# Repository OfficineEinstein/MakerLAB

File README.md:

# MakerLAB
Demo board didattica per i laboratori di Tecnologie e Progettazione di Sistemi Elettronici (TPSE):  elettronica digitale e microcontrollori

Il laboratorio portatile finalmente operativo

Video testing of the MakerLAB

https://youtu.be/5uMLk8OzwR4

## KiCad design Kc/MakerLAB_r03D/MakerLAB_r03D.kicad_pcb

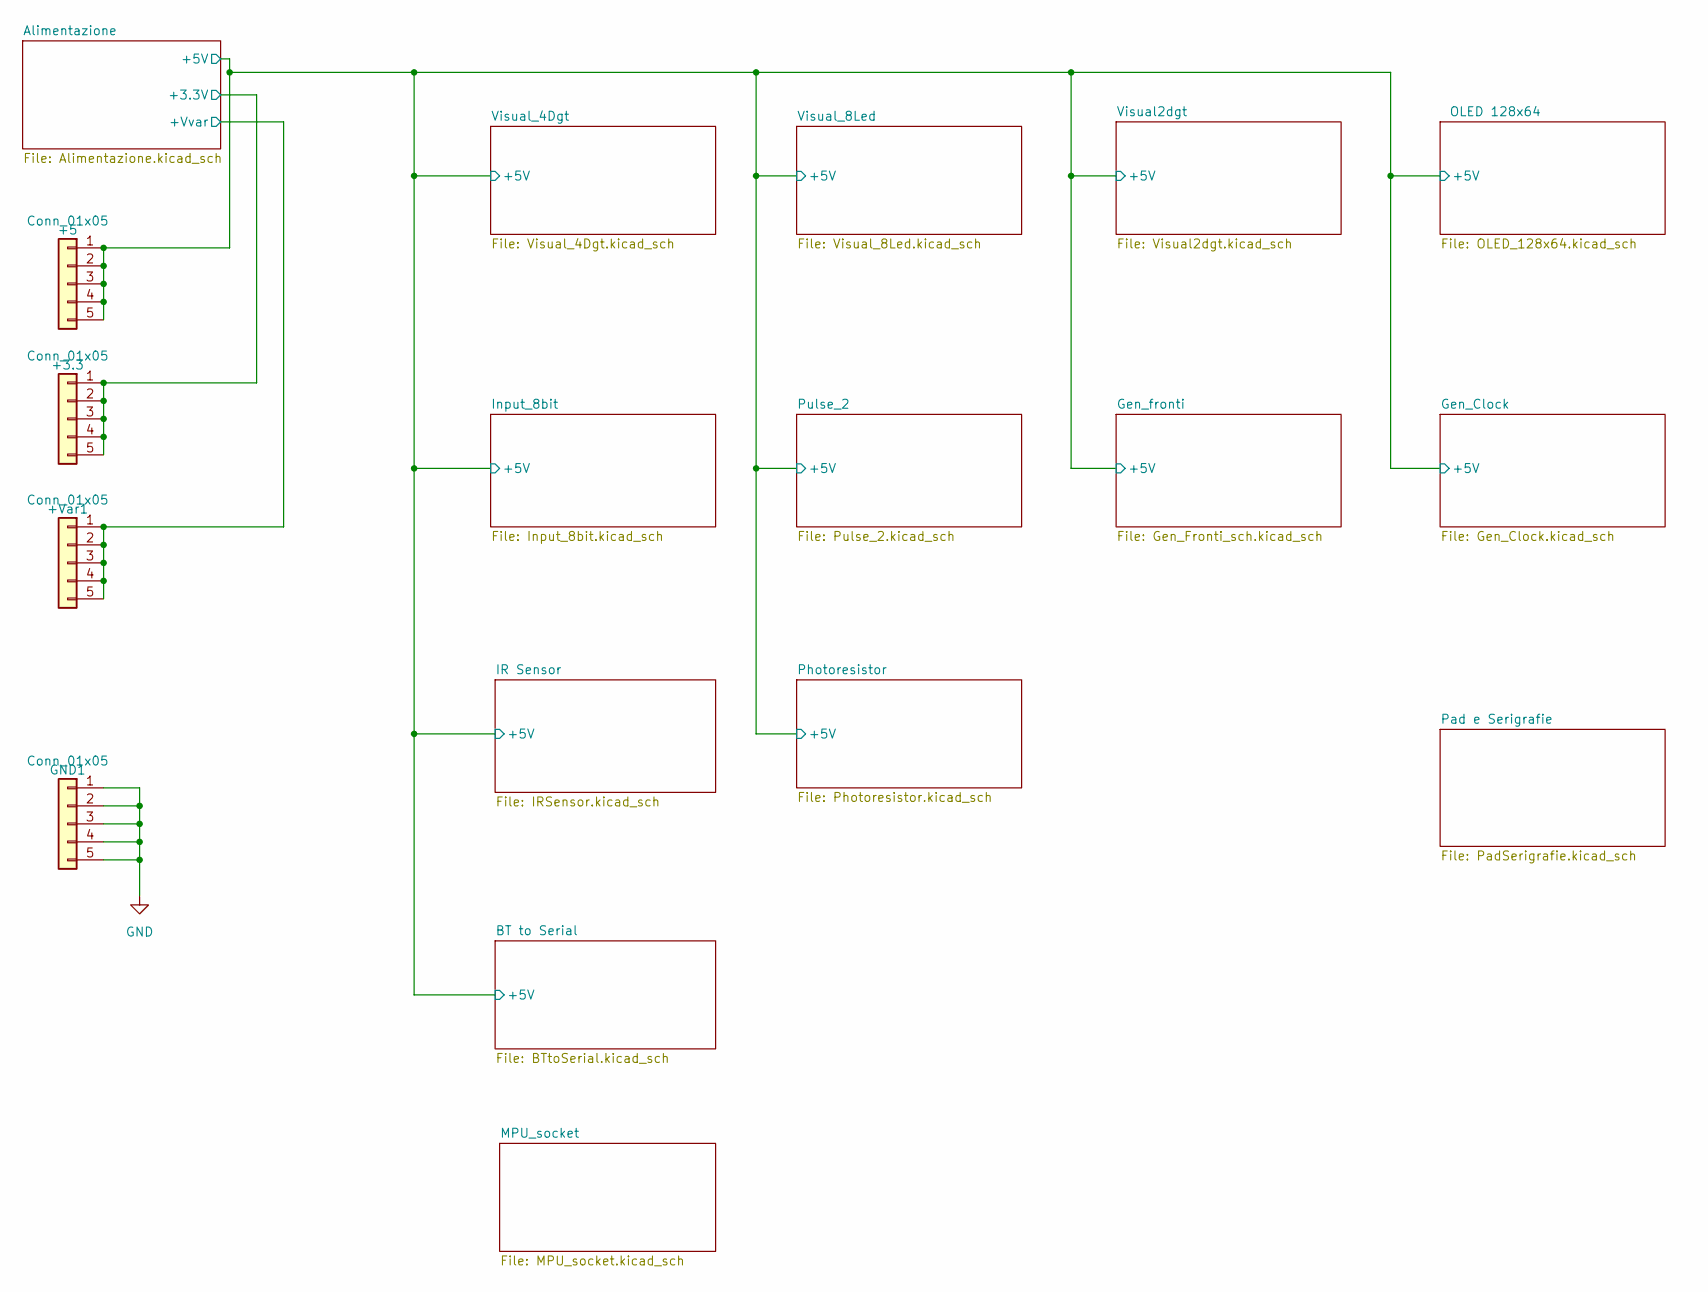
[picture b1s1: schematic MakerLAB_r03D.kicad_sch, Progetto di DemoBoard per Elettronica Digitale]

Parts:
+3.3, +5: Conn_01x05; PinHeader_1x05_P2.54mm_Vertical
+Var1: Conn_01x05; PinHeader_1x05_P2.54mm_Vertical
GND1: Conn_01x05; PinHeader_1x05_P2.54mm_Vertical

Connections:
/Alimentazione/+3.3V: +3.3.1, +3.3.2, +3.3.3, +3.3.4, +3.3.5; also elsewhere on the board
/Alimentazione/+5V: +5.1, +5.2, +5.3, +5.4, +5.5; also elsewhere on the board
/Alimentazione/+Vvar: +Var1.1, +Var1.2, +Var1.3, +Var1.4, +Var1.5; also elsewhere on the board

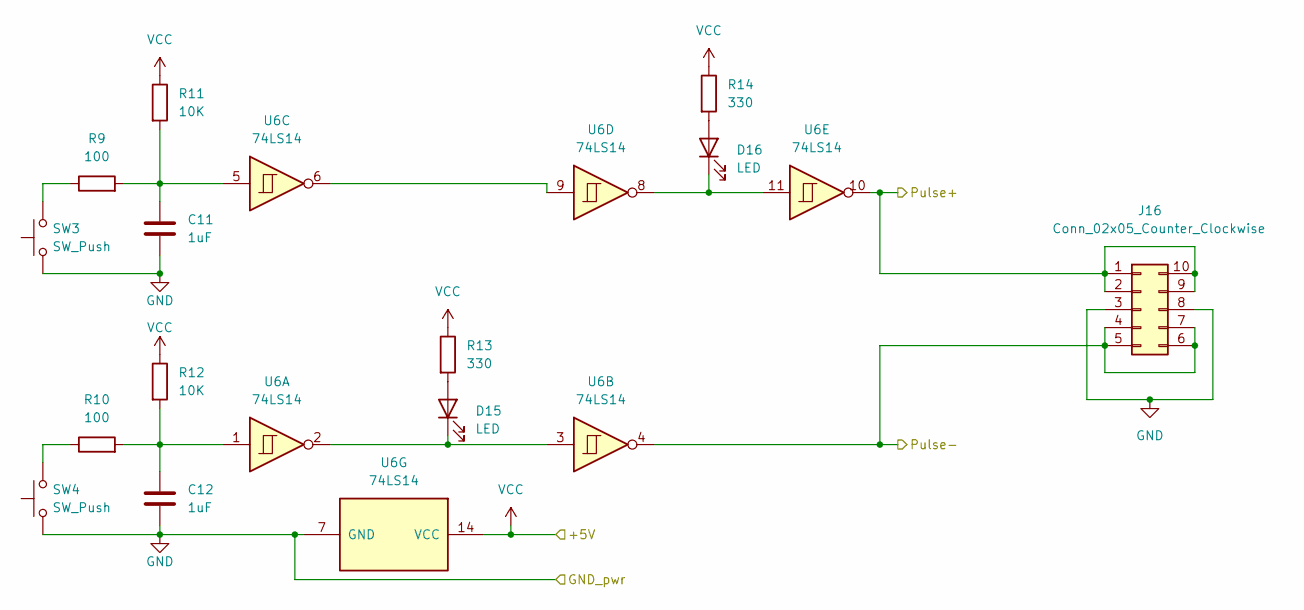
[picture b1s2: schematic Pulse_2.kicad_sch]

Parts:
C11, C12: 1uF
D15, D16: LED
J16: Conn_02x05_Counter_Clockwise; PinSocket_2x05_P2.54mm_Vertical
R9, R10: 100
R11, R12: 10K
R13, R14: 330
SW3, SW4: SW_Push
U6: 74LS14

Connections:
/Alimentazione/+5V: R11.1, R12.1, R13.1, R14.1, U6.14 (VCC); also elsewhere on the board
unnamed: C11.1, R9.2, R11.2, U6.5
unnamed: C12.1, R10.2, R12.2, U6.1
unnamed: D15.1 (K), U6.2, U6.3
unnamed: D15.2 (A), R13.2
unnamed: D16.1 (K), U6.8, U6.11
unnamed: D16.2 (A), R14.2
unnamed: R9.1, SW3.2
unnamed: R10.1, SW4.2
unnamed: U6.6, U6.9

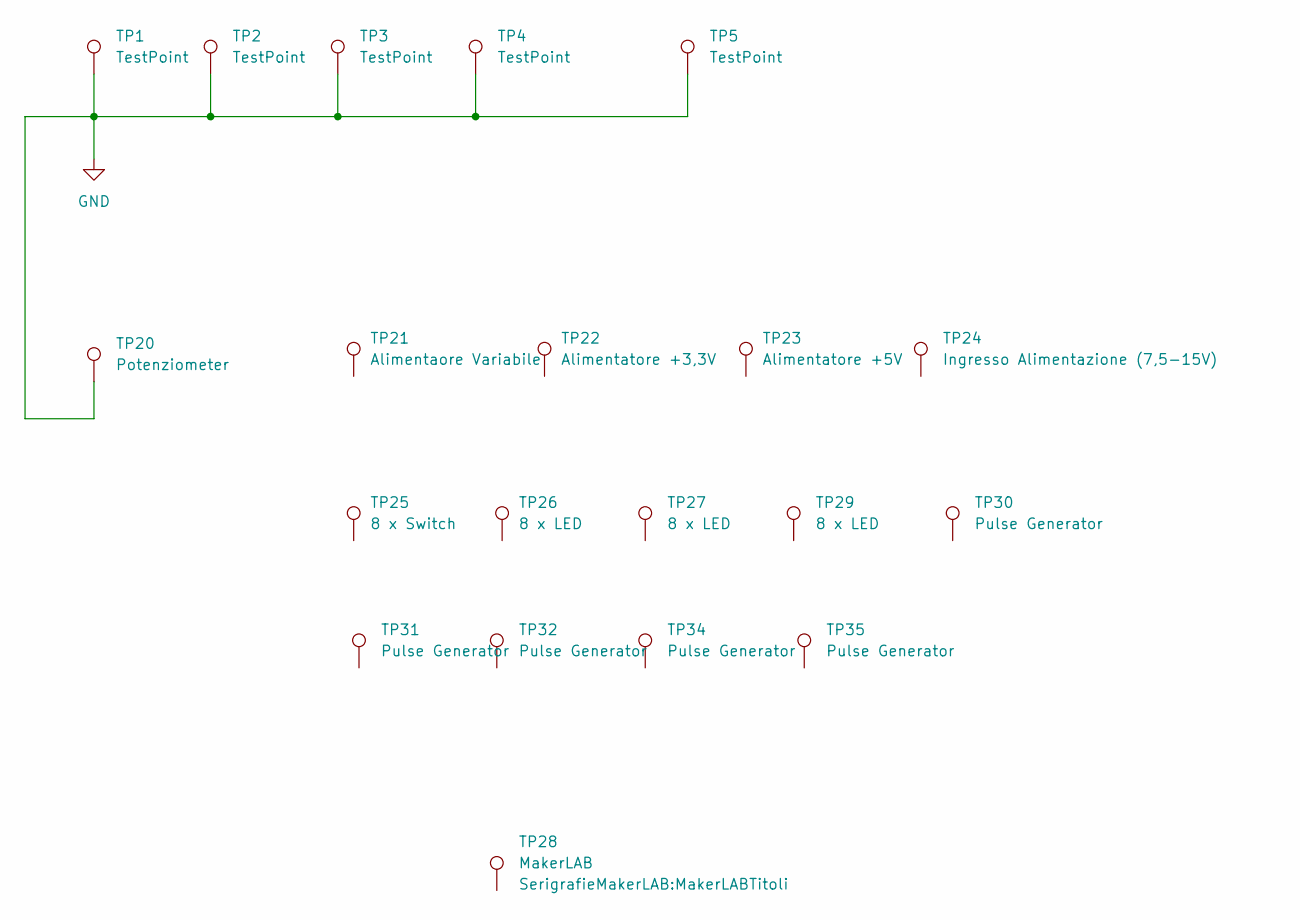
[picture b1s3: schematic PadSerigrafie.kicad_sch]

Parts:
TP1, TP2, TP3, TP4: TestPoint; MountingHole_3.2mm_M3_Pad_Via
TP5: TestPoint; BreadBoard 81x146
TP20: Potenziometer; MountingHole_6.5mm_Pad_Via
TP21: Alimentaore Variabile; Alimentatore Variabile
TP22: Alimentatore +3,3V; Alimentatore Variabile
TP23: Alimentatore +5V; Alimentatore Variabile
TP24: Ingresso Alimentazione (7,5-15V); Alimentatore Variabile
TP25: 8 x Switch; Alimentatore Variabile
TP26: 8 x LED; Alimentatore Variabile
TP27: 8 x LED; Disp4x7Seg
TP28: MakerLAB; MakerLABTitoli
TP29: 8 x LED; Clock NE555
TP30: Pulse Generator; Clock NE555
TP31, TP32, TP34, TP35: Pulse Generator; Disp4x7Seg

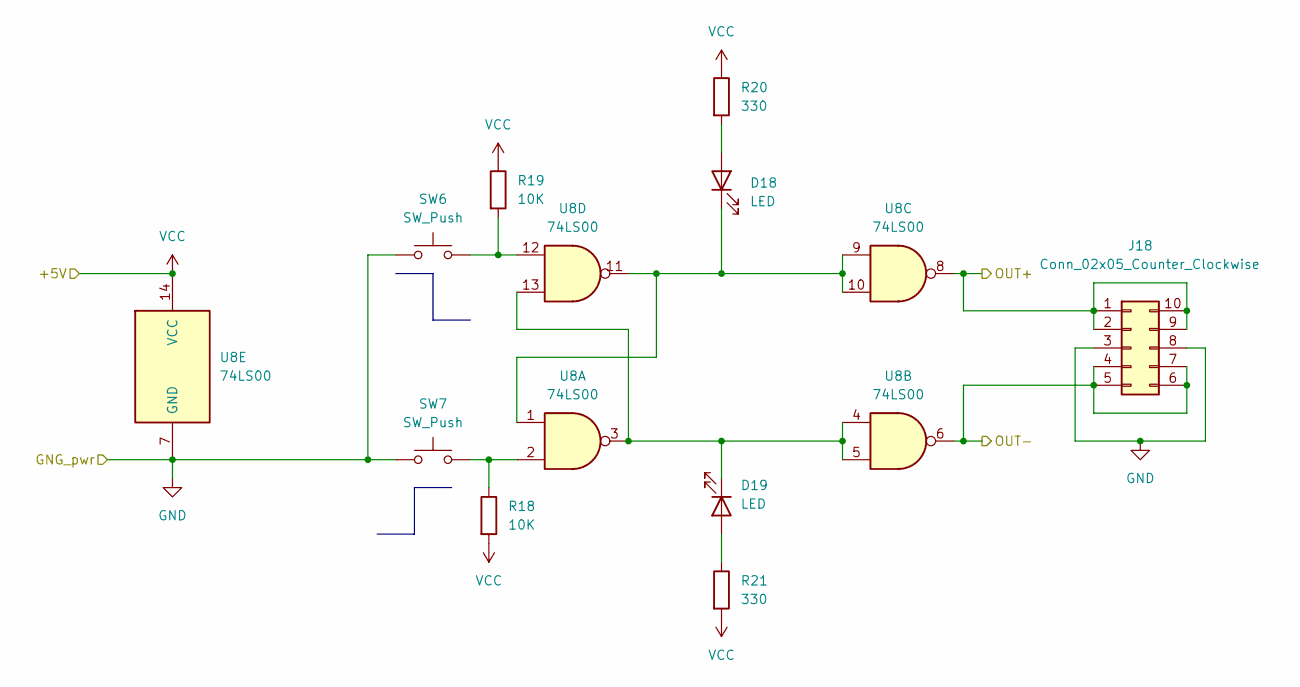
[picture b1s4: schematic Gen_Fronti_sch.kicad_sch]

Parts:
D18, D19: LED
J18: Conn_02x05_Counter_Clockwise; PinSocket_2x05_P2.54mm_Vertical
R18, R19: 10K
R20, R21: 330
SW6, SW7: SW_Push
U8: 74LS00

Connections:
/Alimentazione/+5V: R18.2, R19.1, R20.1, R21.2, U8.14 (VCC); also elsewhere on the board
unnamed: D18.1 (K), U8.1, U8.9, U8.10, U8.11
unnamed: D18.2 (A), R20.2
unnamed: D19.1 (K), U8.3, U8.4, U8.5, U8.13
unnamed: D19.2 (A), R21.1
unnamed 61: J18.1, J18.2, J18.9, J18.10, U8.8; also elsewhere on the board
unnamed 62: J18.4, J18.5, J18.6, J18.7, U8.6; also elsewhere on the board
unnamed: R18.1, SW7.2, U8.2
unnamed: R19.2, SW6.2, U8.12

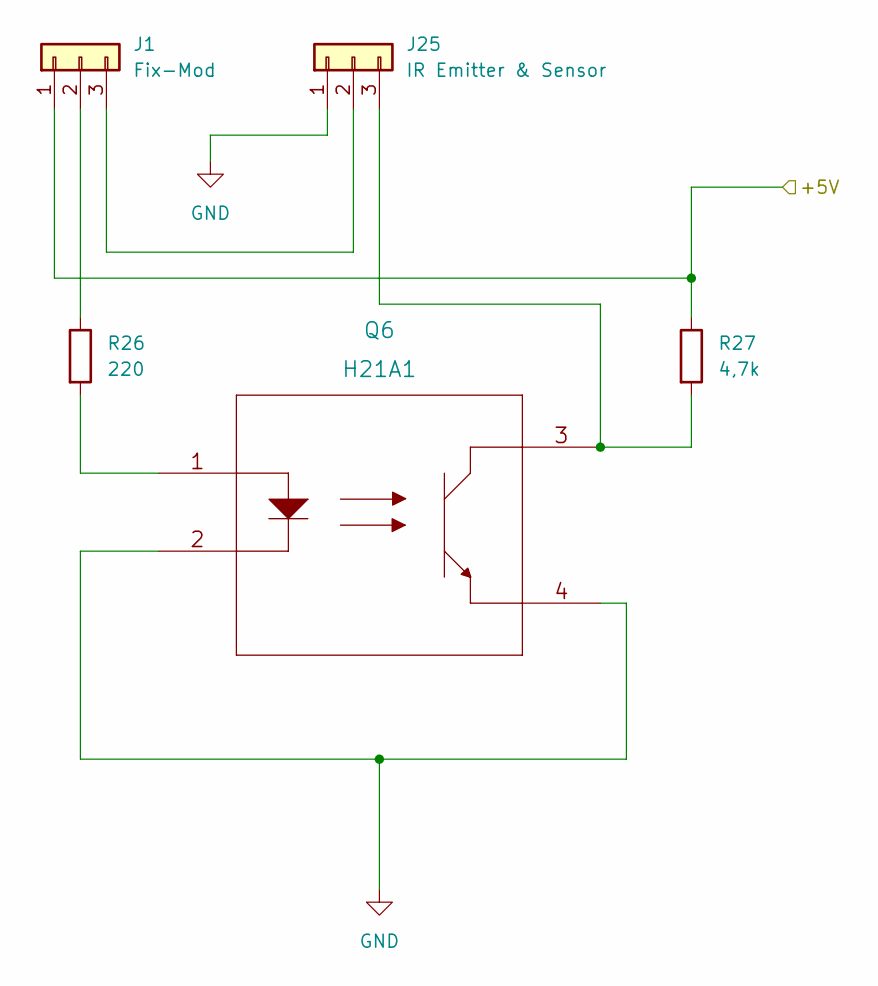
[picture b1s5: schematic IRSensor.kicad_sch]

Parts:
J1: Fix-Mod; PinHeader_1x03_P2.54mm_Vertical
J25: IR Emitter & Sensor; PinHeader_1x03_P2.54mm_Vertical
Q6: H21A1
R26: 220; R_Axial_DIN0207_L6.3mm_D2.5mm_P10.16mm_Horizontal
R27: 4,7k; R_Axial_DIN0207_L6.3mm_D2.5mm_P10.16mm_Horizontal

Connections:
/Alimentazione/+5V: J1.1, R27.1; also elsewhere on the board
unnamed: J1.2, R26.1
unnamed: J1.3, J25.2
unnamed: J25.3, Q6.3, R27.2
unnamed: Q6.1, R26.2

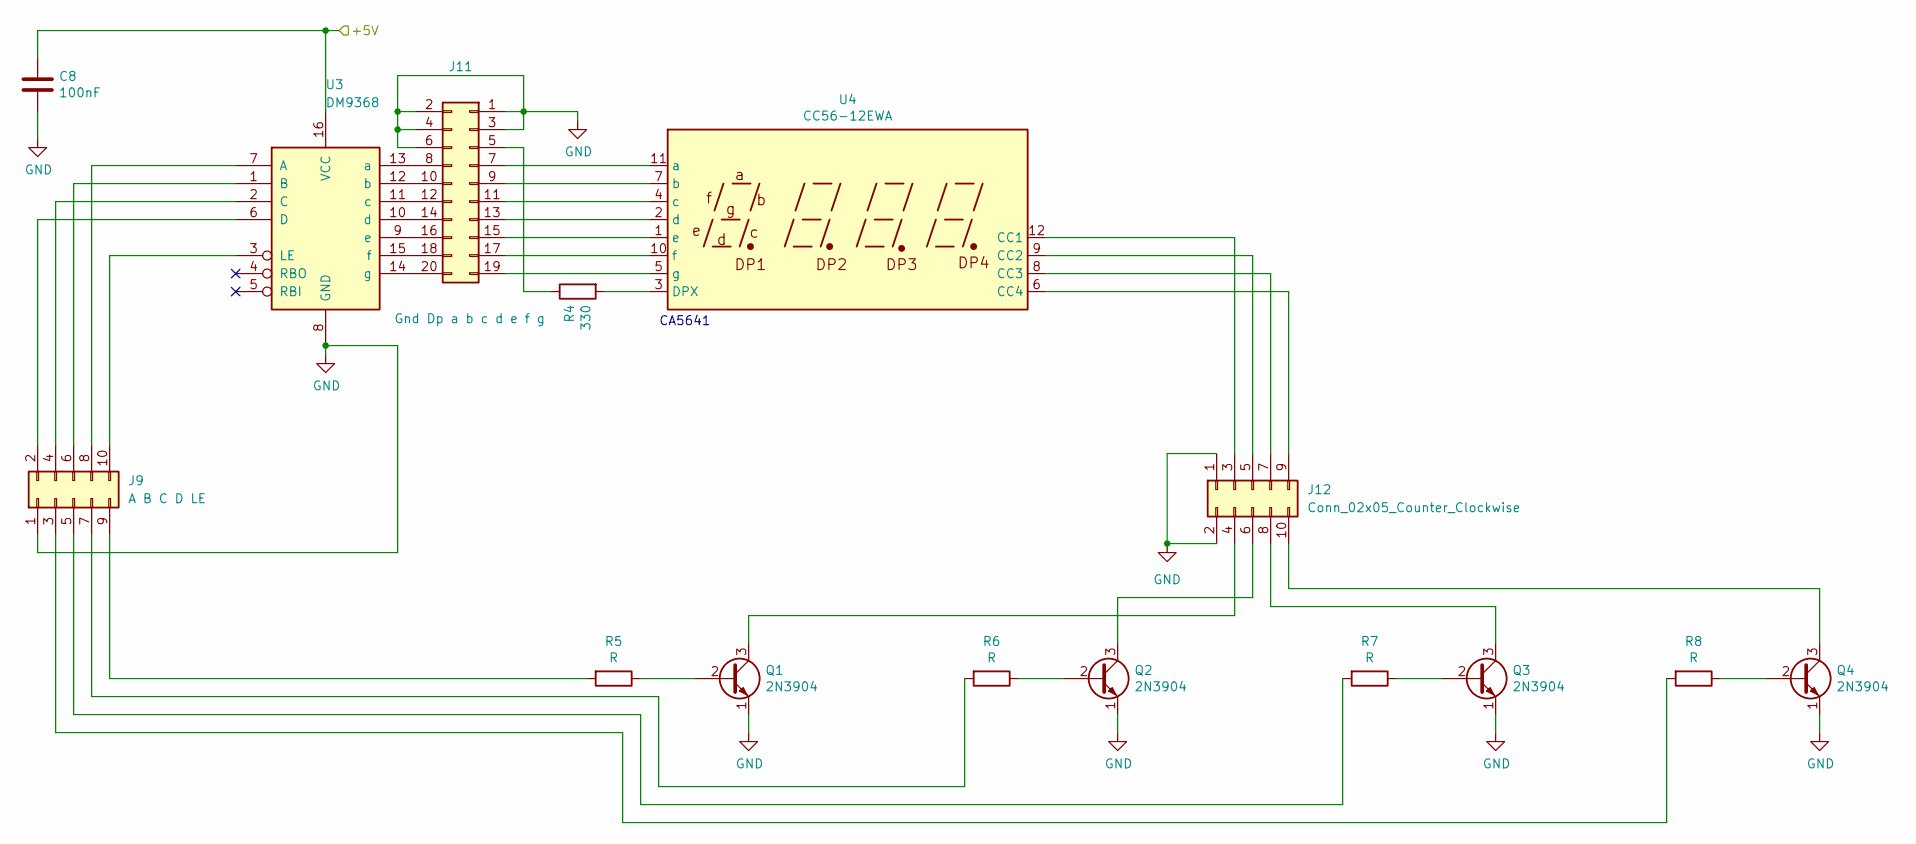
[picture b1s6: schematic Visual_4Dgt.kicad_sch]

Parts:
C8: 100nF; C_Disc_D7.5mm_W2.5mm_P5.00mm
J9: A B C D LE; PinSocket_2x05_P2.54mm_Vertical
J11: Gnd Dp a b c d e f g; PinSocket_2x10_P2.54mm_Vertical
J12: Conn_02x05_Counter_Clockwise; PinSocket_2x05_P2.54mm_Vertical
Q1, Q2, Q3, Q4: 2N3904; TO-92_Inline
R4: 330; R_Axial_DIN0207_L6.3mm_D2.5mm_P10.16mm_Horizontal
R5, R6, R7, R8: R; R_Axial_DIN0207_L6.3mm_D2.5mm_P10.16mm_Horizontal
U3: DM9368; DIP-16_W7.62mm_LongPads
U4: CC56-12EWA; CA56-12EWA

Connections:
/Alimentazione/+5V: C8.1, U3.16 (VCC); also elsewhere on the board
unnamed: J9.2, U3.6 (D)
unnamed: J9.3, R8.2
unnamed: J9.4, U3.2 (C)
unnamed: J9.5, R7.2
unnamed: J9.6, U3.1 (B)
unnamed: J9.7, R6.2
unnamed: J9.8, U3.7 (A)
unnamed: J9.9, R5.2
unnamed: J9.10, U3.3 (LE)
unnamed: J11.5, R4.1
unnamed: J11.7, U4.11 (a)
unnamed: J11.8, U3.13 (a)
unnamed: J11.9, U4.7 (b)
unnamed: J11.10, U3.12 (b)
unnamed: J11.11, U4.4 (c)
unnamed: J11.12, U3.11 (c)
unnamed: J11.13, U4.2 (d)
unnamed: J11.14, U3.10 (d)
unnamed: J11.15, U4.1 (e)
unnamed: J11.16, U3.9 (e)
unnamed: J11.17, U4.10 (f)
unnamed: J11.18, U3.15 (f)
unnamed: J11.19, U4.5 (g)
unnamed: J11.20, U3.14 (g)
unnamed: J12.3, U4.12 (CC1)
unnamed: J12.4, Q1.3 (C)
unnamed: J12.5, U4.9 (CC2)
unnamed: J12.6, Q2.3 (C)
unnamed: J12.7, U4.8 (CC3)
unnamed: J12.8, Q3.3 (C)
unnamed: J12.9, U4.6 (CC4)
unnamed: J12.10, Q4.3 (C)
unnamed: Q1.2 (B), R5.1
unnamed: Q2.2 (B), R6.1
unnamed: Q3.2 (B), R7.1
unnamed: Q4.2 (B), R8.1
unnamed: R4.2, U4.3 (DPX)

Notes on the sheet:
CA5641

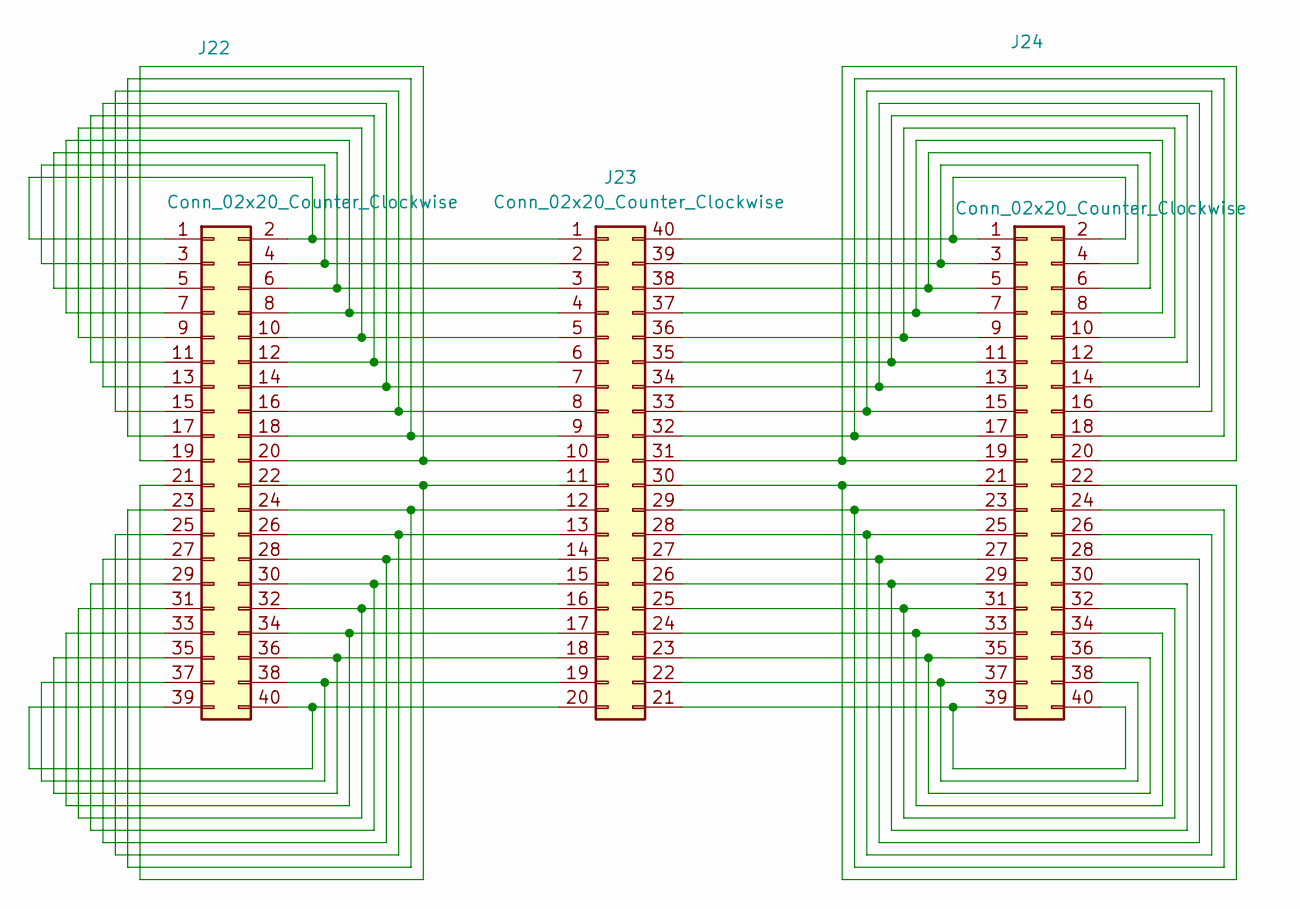
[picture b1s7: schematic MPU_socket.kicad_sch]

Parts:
J22, J24: Conn_02x20_Counter_Clockwise; PinSocket_2x20_P2.54mm_Vertical
J23: Conn_02x20_Counter_Clockwise; DIP_Socket-40_W22.1_W22.86_W25.4_W27.94_W28.7_3M_240-3639-0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

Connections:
unnamed: J22.1, J22.2, J23.1
unnamed: J22.3, J22.4, J23.2
unnamed: J22.5, J22.6, J23.3
unnamed: J22.7, J22.8, J23.4
unnamed: J22.9, J22.10, J23.5
unnamed: J22.11, J22.12, J23.6
unnamed: J22.13, J22.14, J23.7
unnamed: J22.15, J22.16, J23.8
unnamed: J22.17, J22.18, J23.9
unnamed: J22.19, J22.20, J23.10
unnamed: J22.21, J22.22, J23.11
unnamed: J22.23, J22.24, J23.12
unnamed: J22.25, J22.26, J23.13
unnamed: J22.27, J22.28, J23.14
unnamed: J22.29, J22.30, J23.15
unnamed: J22.31, J22.32, J23.16
unnamed: J22.33, J22.34, J23.17
unnamed: J22.35, J22.36, J23.18
unnamed: J22.37, J22.38, J23.19
unnamed: J22.39, J22.40, J23.20
unnamed: J23.21, J24.39, J24.40
unnamed: J23.22, J24.37, J24.38
unnamed: J23.23, J24.35, J24.36
unnamed: J23.24, J24.33, J24.34
unnamed: J23.25, J24.31, J24.32
unnamed: J23.26, J24.29, J24.30
unnamed: J23.27, J24.27, J24.28
unnamed: J23.28, J24.25, J24.26
unnamed: J23.29, J24.23, J24.24
unnamed: J23.30, J24.21, J24.22
unnamed: J23.31, J24.19, J24.20
unnamed: J23.32, J24.17, J24.18
unnamed: J23.33, J24.15, J24.16
unnamed: J23.34, J24.13, J24.14
unnamed: J23.35, J24.11, J24.12
unnamed: J23.36, J24.9, J24.10
unnamed: J23.37, J24.7, J24.8
unnamed: J23.38, J24.5, J24.6
unnamed: J23.39, J24.3, J24.4
unnamed: J23.40, J24.1, J24.2

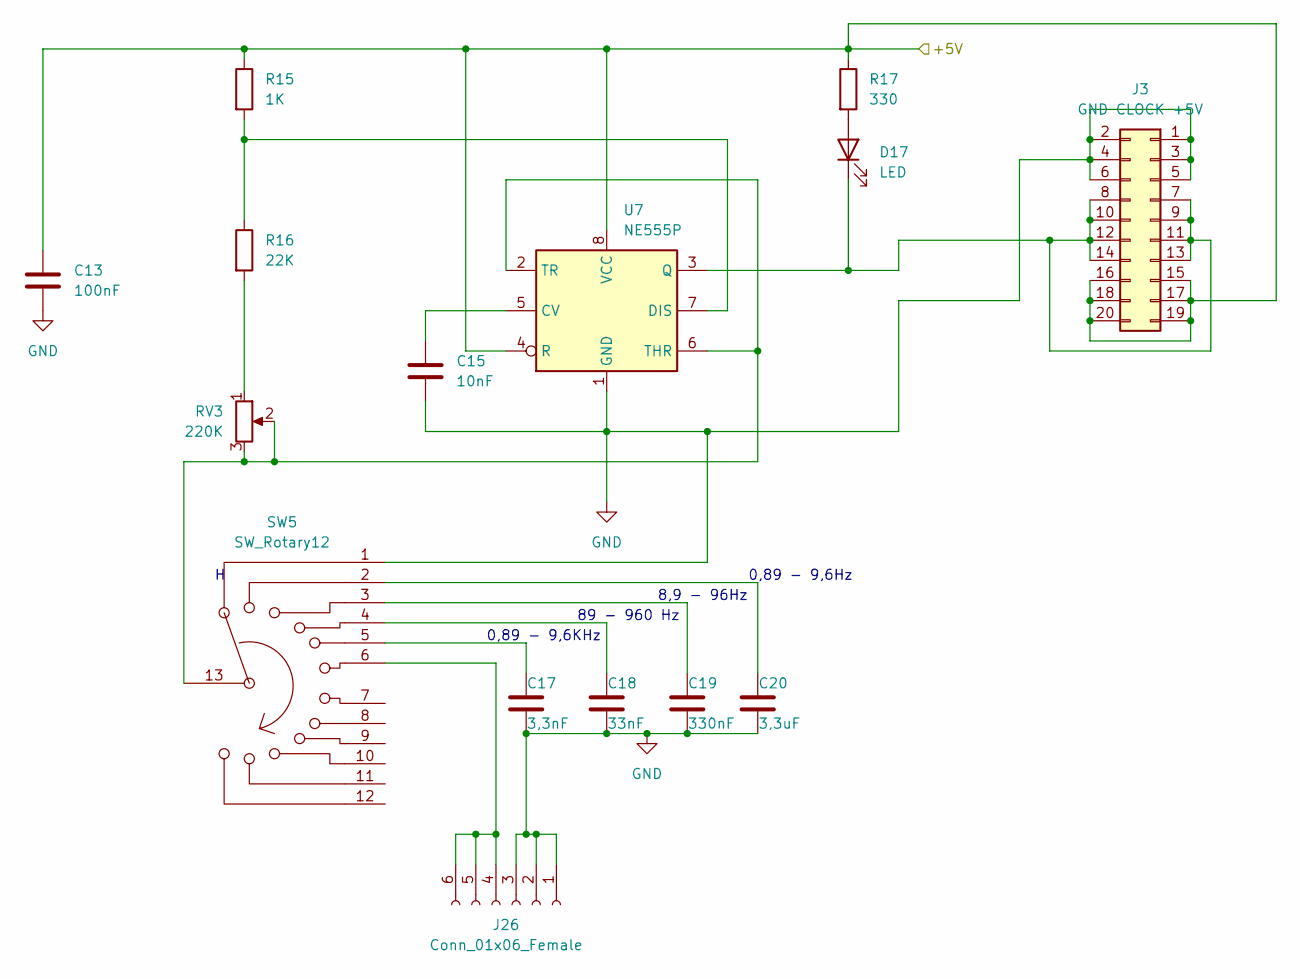
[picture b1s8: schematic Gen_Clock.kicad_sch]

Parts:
C13: 100nF; C_Axial_L5.1mm_D3.1mm_P7.50mm_Horizontal
C15: 10nF; C_Axial_L5.1mm_D3.1mm_P7.50mm_Horizontal
C17: 3,3nF; C_Axial_L5.1mm_D3.1mm_P7.50mm_Horizontal
C18: 33nF; C_Axial_L5.1mm_D3.1mm_P7.50mm_Horizontal
C19: 330nF; C_Axial_L5.1mm_D3.1mm_P7.50mm_Horizontal
C20: 3,3uF; C_Axial_L5.1mm_D3.1mm_P7.50mm_Horizontal
D17: LED; LED_D5.0mm
J3: GND CLOCK +5V; PinSocket_2x10_P2.54mm_Vertical
J26: Conn_01x06_Female; PinHeader_1x06_P2.54mm_Vertical
R15: 1K; R_Axial_DIN0207_L6.3mm_D2.5mm_P10.16mm_Horizontal
R16: 22K; R_Axial_DIN0207_L6.3mm_D2.5mm_P10.16mm_Horizontal
R17: 330; R_Axial_DIN0207_L6.3mm_D2.5mm_P10.16mm_Horizontal
RV3: 220K; Potentiometer_ACP_CA14V-15_Vertical
SW5: SW_Rotary12; Commutatore 2x6
U7: NE555P; DIP-8_W7.62mm

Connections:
/Alimentazione/+5V: C13.1, J3.15, J3.16, J3.17, J3.18, J3.19, J3.20, R15.1, R17.1, U7.4 (R), U7.8 (VCC); also elsewhere on the board
unnamed: C15.1, U7.5 (CV)
unnamed: C17.1, SW5.5
unnamed: C18.1, SW5.4
unnamed: C19.1, SW5.3
unnamed: C20.1, SW5.2
unnamed: D17.1 (K), J3.7, J3.8, J3.9, J3.10, J3.11, J3.12, J3.13, J3.14, U7.3 (Q)
unnamed: D17.2 (A), R17.2
unnamed: J26.4, J26.5, J26.6, SW5.6
unnamed: R15.2, R16.1, U7.7 (DIS)
unnamed: R16.2, RV3.1
unnamed: RV3.2, RV3.3, SW5.13, U7.2 (TR), U7.6 (THR)

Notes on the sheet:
0,89 - 9,6Hz
0,89 - 9,6KHz
8,9 - 96Hz
89 - 960 Hz

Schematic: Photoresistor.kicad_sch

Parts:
J33: Visible Light Sensor; PinHeader_1x03_P2.54mm_Vertical
R28: Left; R_LDR_5.0x4.1mm_P3mm_Vertical
R29: Right; R_LDR_5.0x4.1mm_P3mm_Vertical
R30: 33k; R_Axial_DIN0207_L6.3mm_D2.5mm_P10.16mm_Horizontal
R31: Mono; R_LDR_5.0x4.1mm_P3mm_Vertical

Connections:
/Alimentazione/+5V: R28.1, R30.1; also elsewhere on the board
unnamed: J33.2, R28.2, R29.1
unnamed: J33.3, R30.2, R31.1

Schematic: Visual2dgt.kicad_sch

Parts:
AFF1, AFF2: LTS-6980HR; 7SegmentLED_LTS6760_LTS6780
C21, C22: 100n; C_Disc_D4.3mm_W1.9mm_P5.00mm
J19: Conn_01x10_Female; PinHeader_1x10_P2.54mm_Vertical
J20: Screw_Terminal_01x02; TerminalBlock_bornier-2_P5.08mm
U9, U10: 9368; DIP-16_W7.62mm_Socket_LongPads
Uni-A0, Uni-A1, Uni-A2, Uni-A3, Uni-A4: Jumper_3_Open; PinSocket_1x03_P2.54mm_Vertical

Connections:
/Alimentazione/+5V: C21.1, C22.1, J20.1, U9.16 (Vcc), U10.16 (Vcc); also elsewhere on the board
unnamed: AFF1.1 (e), U9.9 (e)
unnamed: AFF1.2 (d), U9.10 (d)
unnamed: AFF1.4 (c), U9.11 (c)
unnamed: AFF1.6 (b), U9.12 (b)
unnamed: AFF1.7 (a), U9.13 (a)
unnamed: AFF1.9 (f), U9.15 (f)
unnamed: AFF1.10 (g), U9.14 (g)
unnamed: AFF2.1 (e), U10.9 (e)
unnamed: AFF2.2 (d), U10.10 (d)
unnamed: AFF2.4 (c), U10.11 (c)
unnamed: AFF2.6 (b), U10.12 (b)
unnamed: AFF2.7 (a), U10.13 (a)
unnamed: AFF2.9 (f), U10.15 (f)
unnamed: AFF2.10 (g), U10.14 (g)
unnamed: J19.1, U10.3 (LE-)
unnamed: J19.2, Uni-A0.1 (A)
unnamed: J19.3, Uni-A1.1 (A)
unnamed: J19.4, Uni-A2.1 (A)
unnamed: J19.5, Uni-A3.1 (A)
unnamed: J19.6, U9.7 (A0), Uni-A0.3 (B)
unnamed: J19.7, U9.1 (A1), Uni-A1.3 (B)
unnamed: J19.8, U9.2 (A2), Uni-A2.3 (B)
unnamed: J19.9, U9.6 (A3), Uni-A3.3 (B)
unnamed: J19.10, U9.3 (LE-)
unnamed: U9.5 (RBI-), Uni-A4.2 (C)
unnamed: U10.1 (A1), Uni-A1.2 (C)
unnamed: U10.2 (A2), Uni-A2.2 (C)
unnamed: U9.4 (RBO-), U10.5 (RBI-)
unnamed: U10.6 (A3), Uni-A3.2 (C)
unnamed: U10.7 (A0), Uni-A0.2 (C)

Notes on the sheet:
unità
decine
Rbo_Off

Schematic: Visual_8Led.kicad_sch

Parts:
C9: 100nF; C_Axial_L3.8mm_D2.6mm_P7.50mm_Horizontal
D7: 7; LED_D5.0mm
D8: 6; LED_D5.0mm
D9: 5; LED_D5.0mm
D10: 4; LED_D5.0mm
D11: 3; LED_D5.0mm
D12: 2; LED_D5.0mm
D13: 1; LED_D5.0mm
D14: 0; LED_D5.0mm
J13: GND 0 1 2 3 4 5 6 7 +5V; PinSocket_1x10_P2.54mm_Vertical
J14: 8Bit Jumper; PinSocket_2x10_P2.54mm_Vertical
RN1: 330; DIP-16_W7.62mm_Socket_LongPads
TP6: Bit0; TestPoint_Loop_D3.80mm_Drill2.8mm
TP7: Bit1; TestPoint_Loop_D3.80mm_Drill2.8mm
TP8: Bit2; TestPoint_Loop_D3.80mm_Drill2.8mm
TP9: Bit3; TestPoint_Loop_D3.80mm_Drill2.8mm
TP10: Bit4; TestPoint_Loop_D3.80mm_Drill2.8mm
TP11: Bit5; TestPoint_Loop_D3.80mm_Drill2.8mm
TP12: Bit6; TestPoint_Loop_D3.80mm_Drill2.8mm
TP13: Bit7; TestPoint_Loop_D3.80mm_Drill2.8mm
U5: ULN2803A; DIP-18_W7.62mm_Socket_LongPads

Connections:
/Alimentazione/+5V: C9.2, D7.2 (A), D8.2 (A), D9.2 (A), D10.2 (A), D11.2 (A), D12.2 (A), D13.2 (A), D14.2 (A), J13.10, J14.20; also elsewhere on the board
unnamed: D7.1 (K), RN1.16 (R1.2), TP13.1
unnamed: D8.1 (K), RN1.15 (R2.2), TP12.1
unnamed: D9.1 (K), RN1.14 (R3.2), TP11.1
unnamed: D10.1 (K), RN1.13 (R4.2), TP10.1
unnamed: D11.1 (K), RN1.12 (R5.2), TP9.1
unnamed: D12.1 (K), RN1.11 (R6.2), TP8.1
unnamed: D13.1 (K), RN1.10 (R7.2), TP7.1
unnamed: D14.1 (K), RN1.9 (R8.2), TP6.1
unnamed: J13.2, U5.1 (I1)
unnamed: J13.3, U5.2 (I2)
unnamed: J13.4, U5.3 (I3)
unnamed: J13.5, U5.4 (I4)
unnamed: J13.6, U5.5 (I5)
unnamed: J13.7, U5.6 (I6)
unnamed: J13.8, U5.7 (I7)
unnamed: J13.9, U5.8 (I8)
unnamed: J14.3, U5.11 (O8)
unnamed: J14.4, RN1.8 (R8.1)
unnamed: J14.5, U5.12 (O7)
unnamed: J14.6, RN1.7 (R7.1)
unnamed: J14.7, U5.13 (O6)
unnamed: J14.8, RN1.6 (R6.1)
unnamed: J14.9, U5.14 (O5)
unnamed: J14.10, RN1.5 (R5.1)
unnamed: J14.11, U5.15 (O4)
unnamed: J14.12, RN1.4 (R4.1)
unnamed: J14.13, U5.16 (O3)
unnamed: J14.14, RN1.3 (R3.1)
unnamed: J14.15, U5.17 (O2)
unnamed: J14.16, RN1.2 (R2.1)
unnamed: J14.17, U5.18 (O1)
unnamed: J14.18, RN1.1 (R1.1)
unnamed: J14.19, U5.10 (COM)

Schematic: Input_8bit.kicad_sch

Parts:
C10: 100nF; C_Disc_D7.0mm_W2.5mm_P5.00mm
J15: GND 0 1 2 3 4 5 6 7 +5V; PinSocket_1x10_P2.54mm_Vertical
RN2: 10K; DIP-16_W7.62mm_Socket_LongPads
SW2: SW_DIP_x08; DIP-16_W7.62mm_Socket_LongPads

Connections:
/Alimentazione/+5V: C10.1, J15.10, RN2.9 (R8.2), RN2.10 (R7.2), RN2.11 (R6.2), RN2.12 (R5.2), RN2.13 (R4.2), RN2.14 (R3.2), RN2.15 (R2.2), RN2.16 (R1.2); also elsewhere on the board
unnamed: J15.2, RN2.1 (R1.1), SW2.16
unnamed: J15.3, RN2.2 (R2.1), SW2.15
unnamed: J15.4, RN2.3 (R3.1), SW2.14
unnamed: J15.5, RN2.4 (R4.1), SW2.13
unnamed: J15.6, RN2.5 (R5.1), SW2.12
unnamed: J15.7, RN2.6 (R6.1), SW2.11
unnamed: J15.8, RN2.7 (R7.1), SW2.10
unnamed: J15.9, RN2.8 (R8.1), SW2.9

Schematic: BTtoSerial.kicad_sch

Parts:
D6, D23, D24, D25, D26, D27: 1n4148; D_A-405_P10.16mm_Horizontal
J34: Conn_01x05; PinHeader_1x05_P2.54mm_Vertical
R32, R33: 1K; R_Axial_DIN0207_L6.3mm_D2.5mm_P10.16mm_Horizontal
U12: HC-05 (ZC142200); HC-05 Module Horizontal (ZC14200); PARTREV N/A

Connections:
/Alimentazione/+5V: U12.5 (VCC); also elsewhere on the board
unnamed: D6.2 (A), D23.1 (K)
unnamed: D23.2 (A), D24.1 (K)
unnamed: D25.2 (A), D26.1 (K)
unnamed: D26.2 (A), D27.1 (K)
unnamed: J34.4, U12.6 (EN)
unnamed: J34.5, U12.1 (STATE)
unnamed 193: D6.1 (K), R32.1, U12.2 (RX); also elsewhere on the board
unnamed 194: D25.1 (K), R33.1, U12.3 (TX); also elsewhere on the board

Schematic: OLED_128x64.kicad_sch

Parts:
J21: Conn_01x03; PinHeader_1x03_P2.54mm_Vertical
LCD1: SSD1306_OLED128x64_I2C; TFT OLED 1.3 I2C
R3, R25: 3,3k; R_Axial_DIN0207_L6.3mm_D2.5mm_P10.16mm_Horizontal

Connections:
/Alimentazione/+5V: LCD1.1 (Vcc), R3.2, R25.2; also elsewhere on the board
unnamed: J21.2, LCD1.3 (SCL), R3.1
unnamed: J21.3, LCD1.4 (SDA), R25.1

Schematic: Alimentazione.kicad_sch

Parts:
C1: 1000uF; CP_Radial_D17.0mm_P7.50mm
C2, C3, C5, C16, C23, C24: 100nF; C_Disc_D7.0mm_W2.5mm_P5.00mm
C4: 10uF; CP_Radial_D5.0mm_P2.00mm
C6, C7, C25: 220uF; CP_Radial_D10.0mm_P5.00mm
D1: D_Bridge_+AA-; Diode_Bridge_Vishay_KBL
D2: VarOut; LED_D5.0mm
D3, D5: 1n4001; D_A-405_P10.16mm_Horizontal
D4, D20: 1N4001; D_A-405_P10.16mm_Horizontal
D21: +5V; LED_D5.0mm
D22: +3.3V; LED_D5.0mm
F1: Polyfuse 750mA; RV_Disc_D7mm_W5.4mm_P5mm
HS1, HS2: Heatsink; Heatsink_28x25_Horiz
J4: Barrel_Jack_MountingPin; BarrelJack_Horizontal
J5, J29, J30: Conn_01x02_Male; PinSocket_1x02_P2.54mm_Vertical
L1: 3,3mH; L_Axial_L12.0mm_D5.0mm_P15.24mm_Horizontal_Fastron_MISC
Q5: BC237; TO-92_Inline
R1: 3,3k; R_Axial_DIN0207_L6.3mm_D2.5mm_P10.16mm_Horizontal
R2: 240; R_Axial_DIN0207_L6.3mm_D2.5mm_P10.16mm_Horizontal
R22: 330k; R_Axial_DIN0207_L6.3mm_D2.5mm_P10.16mm_Horizontal
R23: 680; R_Axial_DIN0207_L6.3mm_D2.5mm_P10.16mm_Horizontal
R24: 220; R_Axial_DIN0207_L6.3mm_D2.5mm_P10.16mm_Horizontal
RV2: 5K; Potentiometer_Omeg_PC16BU_Vertical
SW1: SwGenerale; SW_100SP1T2B4M7QE
TP14: VarA+; TestPoint_Loop_D3.80mm_Drill2.8mm
TP15: VarA-; TestPoint_Loop_D3.80mm_Drill2.8mm
TP16: 5VA+; TestPoint_Loop_D3.80mm_Drill2.8mm
TP17: 3.3VA+; TestPoint_Loop_D3.80mm_Drill2.8mm
TP18: 5VA-; TestPoint_Loop_D3.80mm_Drill2.8mm
TP19: 3.3VA-; TestPoint_Loop_D3.80mm_Drill2.8mm
U1: LM317_TO-220; TO-220-3_Horizontal_TabDown
U2: LM7805_TO220; TO-220-3_Horizontal_TabDown
U11: L78L33_SOT89; SOT-223
Vmet1: 3,5_Digit_Voltmeter_3Wire; 3,5 Digit 0,28'' Voltmeter

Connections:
/Alimentazione/+3.3V: J30.2, R24.1, TP19.1; also elsewhere on the board
/Alimentazione/+5V: J29.2, R23.1, TP18.1; also elsewhere on the board
/Alimentazione/+Vvar: C23.1, J5.2, R22.2, TP15.1, Vmet1.2 (Vin); also elsewhere on the board
unnamed: C1.1, C2.1, C3.1, D3.1 (K), D4.1 (K), L1.2, R1.1, U1.3 (VI), U2.1 (VI)
unnamed: C4.1, D5.2 (A), R2.2, RV2.1, U1.1 (ADJ)
unnamed: C7.1, D3.2 (A), D5.1 (K), J5.1, R2.1, TP14.1, U1.2 (VO)
unnamed: C5.1, C6.1, C16.1, D4.2 (A), D20.1 (K), J29.1, TP16.1, U2.3 (VO), U11.3 (IN), Vmet1.3 (V+)
unnamed: C24.1, C25.1, D20.2 (A), J30.1, TP17.1, U11.1 (OUT)
unnamed: D1.1 (+), L1.1
unnamed: D1.2, F1.2
unnamed: D1.3, SW1.3 (C)
unnamed: D2.1 (K), Q5.1 (C)
unnamed: D2.2 (A), R1.2
unnamed: D21.2 (A), R23.2
unnamed: D22.2 (A), R24.2
unnamed: F1.1, J4.1
unnamed: J4.2, SW1.2 (B)
unnamed: Q5.2 (B), R22.1

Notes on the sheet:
MountingHole:Asola

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

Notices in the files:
parts and their libraries:
Copyright 2021 Accelerated Designs. All rights reserved.
